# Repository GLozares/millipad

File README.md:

# MilliPad

## A First Step into the World of Keyboards
Hi there! If you're reading this, thank you for stopping by. This is a repository detailing my first foray into custom mechanical keyboards. I decided to make a custom mechanical keypad to use for myself as my favorite keyboard layout, the 65%, does not have F1 through F12. However, in some circumstances particularly when I am coding, I would like to have those function keys. Thus, instead of buying a numpad off the shelf, I thought it was a great opportunity to make my own.

Prior to this project, I took on a group project in my Computer Engineering senior design class that involves creating our own full sized custom mechanical keyboard. I took some initiative and began to learn PCB design myself as to be a bigger asset to my group down the line.

## Credits
Apart from the dependant repositories already linked in my project, I would like to thank ai03 for their beginner's tutorial on keyboard PCB design. Their guide can be found at https://wiki.ai03.com/books/pcb-design.

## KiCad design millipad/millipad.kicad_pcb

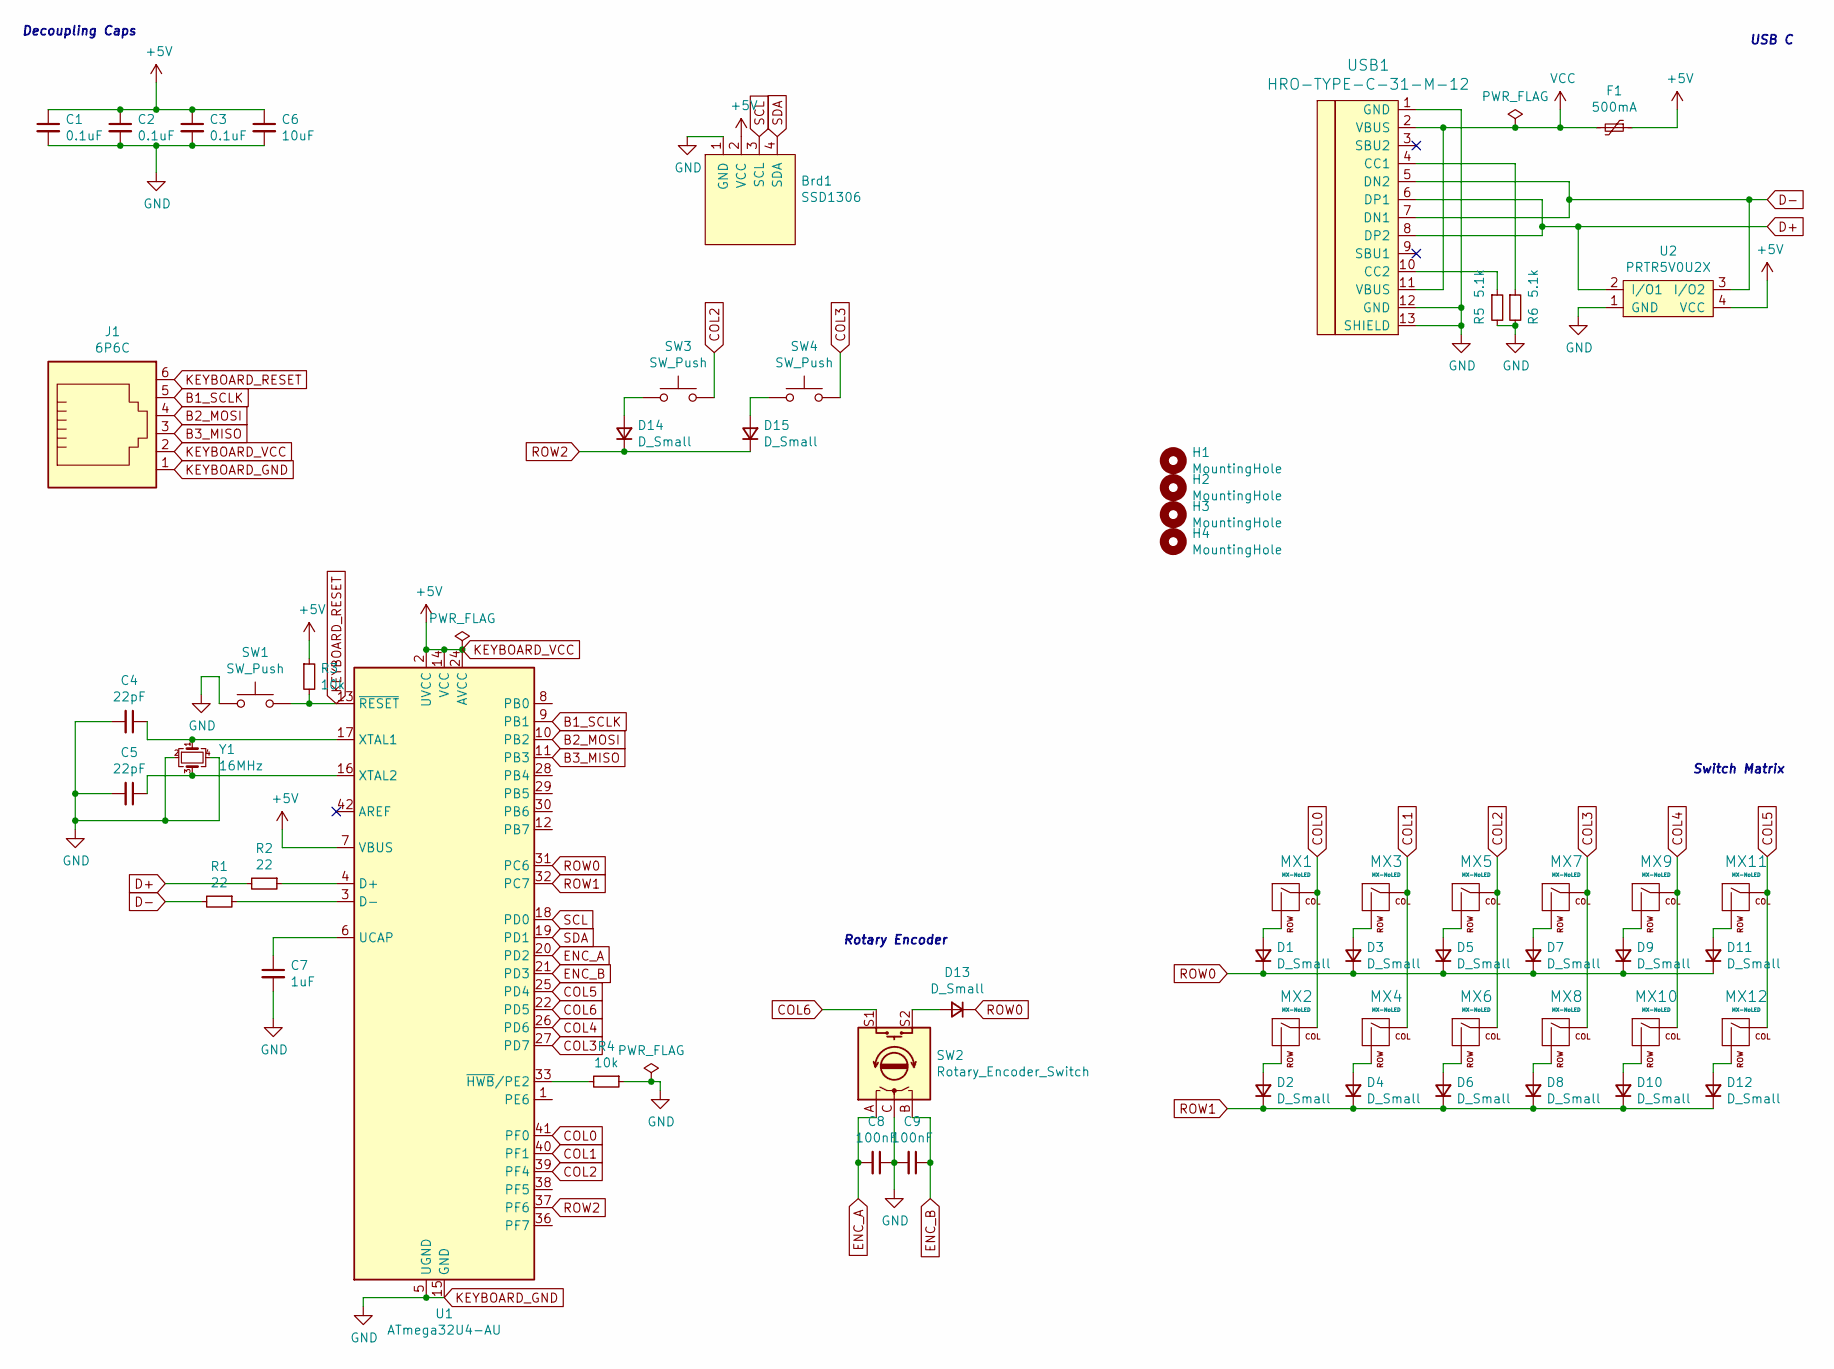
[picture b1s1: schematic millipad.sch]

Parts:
Brd1: SSD1306; 128x64OLED
C1, C2, C3: 0.1uF; C_0805_2012Metric
C4, C5: 22pF; C_0805_2012Metric
C6: 10uF; C_0805_2012Metric
C7: 1uF; C_0805_2012Metric
C8, C9: 100nF; C_0805_2012Metric
D1, D2, D3, D4, D5, D6, D7, D8, D9, D10, D11, D12, D13, D14, D15: D_Small; D_SOD-123
F1: 500mA; Fuse_1206_3216Metric
H1, H2, H3, H4: MountingHole; MountingHole_2.7mm_M2.5
J1: 6P6C; PinSocket_2x03_P1.00mm_Vertical_SMD
MX1, MX2, MX3, MX4, MX5, MX6, MX7, MX8, MX9, MX10, MX11, MX12: MX-NoLED; MXOnly-1U-Hotswap
R1, R2: 22; R_0805_2012Metric
R3, R4: 10k; R_0805_2012Metric
R5, R6: 5.1k; R_0805_2012Metric
SW1, SW3, SW4: SW_Push; SKQG-1155865
SW2: Rotary_Encoder_Switch; RotaryEncoder_Alps_EC11E-Switch_Vertical_H20mm
U1: ATmega32U4-AU; TQFP-44_10x10mm_P0.8mm
U2: PRTR5V0U2X
USB1: HRO-TYPE-C-31-M-12; HRO-TYPE-C-31-M-12-HandSoldering
Y1: 16MHz; Crystal_SMD_3225-4Pin_3.2x2.5mm

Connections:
B1_SCLK: J1.5, U1.9 (PB1)
B2_MOSI: J1.4, U1.10 (PB2)
B3_MISO: J1.3, U1.11 (PB3)
COL0: MX1.1 (COL), MX2.1 (COL), U1.41 (PF0)
COL1: MX3.1 (COL), MX4.1 (COL), U1.40 (PF1)
COL2: MX5.1 (COL), MX6.1 (COL), SW3.2, U1.39 (PF4)
COL3: MX7.1 (COL), MX8.1 (COL), SW4.2, U1.27 (PD7)
COL4: MX9.1 (COL), MX10.1 (COL), U1.26 (PD6)
COL5: MX11.1 (COL), MX12.1 (COL), U1.25 (PD4)
COL6: SW2.S1, U1.22 (PD5)
D+: R2.2, U2.2 (I/O1), USB1.6 (DP1), USB1.8 (DP2)
D-: R1.2, U2.3 (I/O2), USB1.5 (DN2), USB1.7 (DN1)
ENC_A: C8.2, SW2.A, U1.20 (PD2)
ENC_B: C9.1, SW2.B, U1.21 (PD3)
KEYBOARD_GND: Brd1.1 (GND), C1.2, C2.2, C3.2, C4.2, C5.2, C6.2, C7.2, C8.1, C9.2, J1.1, R4.1, R5.2, R6.2, SW1.1, SW2.C, U1.5 (UGND), U1.15 (GND), U1.23 (GND), U1.35 (GND), U1.43 (GND), U2.1 (GND), USB1.1 (GND), USB1.12 (GND), USB1.13 (SHIELD), Y1.2, Y1.4
KEYBOARD_RESET: J1.6, R3.2, SW1.2, U1.13 (~RESET)
KEYBOARD_VCC: Brd1.2 (VCC), C1.1, C2.1, C3.1, C6.1, F1.1, J1.2, R3.1, U1.2 (UVCC), U1.7 (VBUS), U1.14 (VCC), U1.24 (AVCC), U1.34 (VCC), U1.44 (AVCC), U2.4 (VCC)
unnamed: C4.1, U1.17 (XTAL1), Y1.1
unnamed: C5.1, U1.16 (XTAL2), Y1.3
unnamed: C7.1, U1.6 (UCAP)
unnamed: D1.2 (A), MX1.2 (ROW)
unnamed: D2.2 (A), MX2.2 (ROW)
unnamed: D3.2 (A), MX3.2 (ROW)
unnamed: D4.2 (A), MX4.2 (ROW)
unnamed: D5.2 (A), MX5.2 (ROW)
unnamed: D6.2 (A), MX6.2 (ROW)
unnamed: D7.2 (A), MX7.2 (ROW)
unnamed: D8.2 (A), MX8.2 (ROW)
unnamed: D9.2 (A), MX9.2 (ROW)
unnamed: D10.2 (A), MX10.2 (ROW)
unnamed: D11.2 (A), MX11.2 (ROW)
unnamed: D12.2 (A), MX12.2 (ROW)
unnamed: D13.2 (A), SW2.S2
unnamed: D14.2 (A), SW3.1
unnamed: D15.2 (A), SW4.1
unnamed: R1.1, U1.3 (D-)
unnamed: R2.1, U1.4 (D+)
unnamed: R4.2, U1.33 (~HWB~/PE2)
unnamed: R5.1, USB1.10 (CC2)
unnamed: R6.1, USB1.4 (CC1)
ROW0: D1.1 (K), D3.1 (K), D5.1 (K), D7.1 (K), D9.1 (K), D11.1 (K), D13.1 (K), U1.31 (PC6)
ROW1: D2.1 (K), D4.1 (K), D6.1 (K), D8.1 (K), D10.1 (K), D12.1 (K), U1.32 (PC7)
ROW2: D14.1 (K), D15.1 (K), U1.37 (PF6)
SCL: Brd1.3 (SCL), U1.18 (PD0)
SDA: Brd1.4 (SDA), U1.19 (PD1)
VCC: F1.2, USB1.2 (VBUS), USB1.11 (VBUS)

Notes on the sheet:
Decoupling Caps
USB C
Switch Matrix
Rotary Encoder

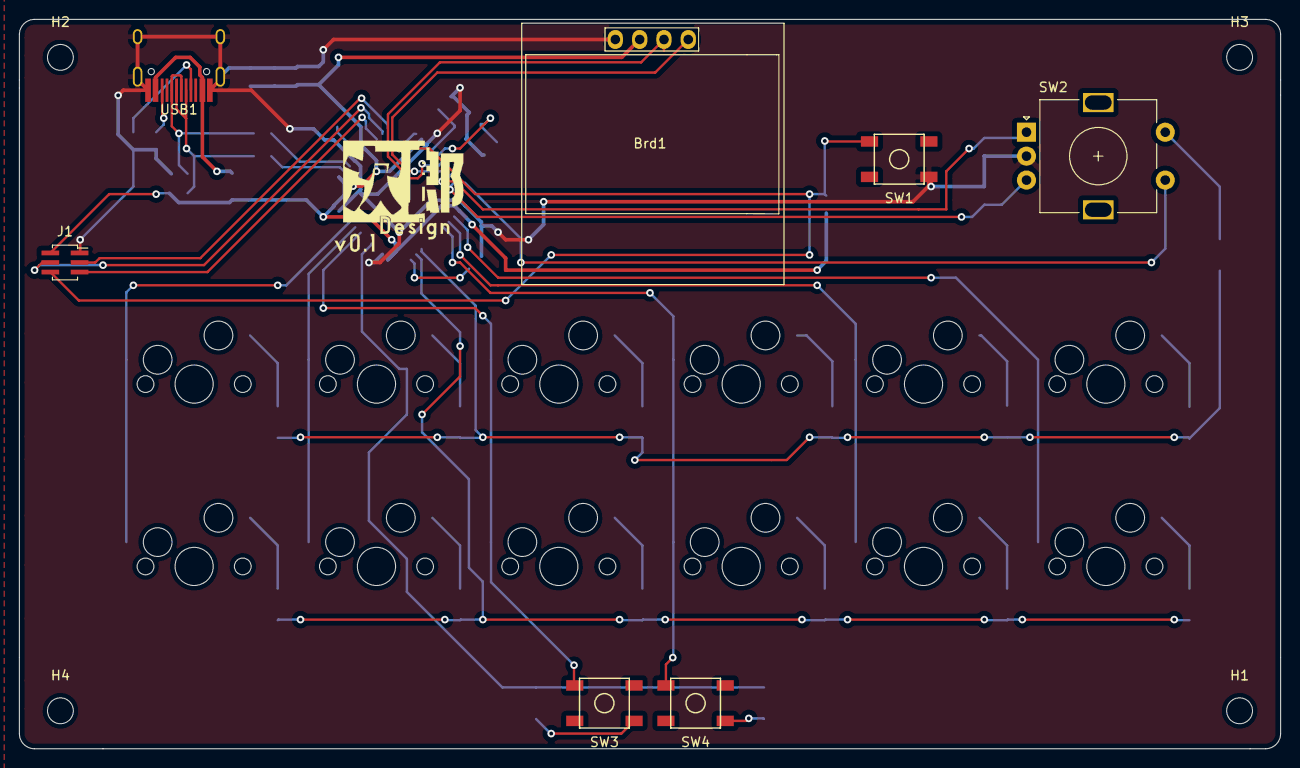
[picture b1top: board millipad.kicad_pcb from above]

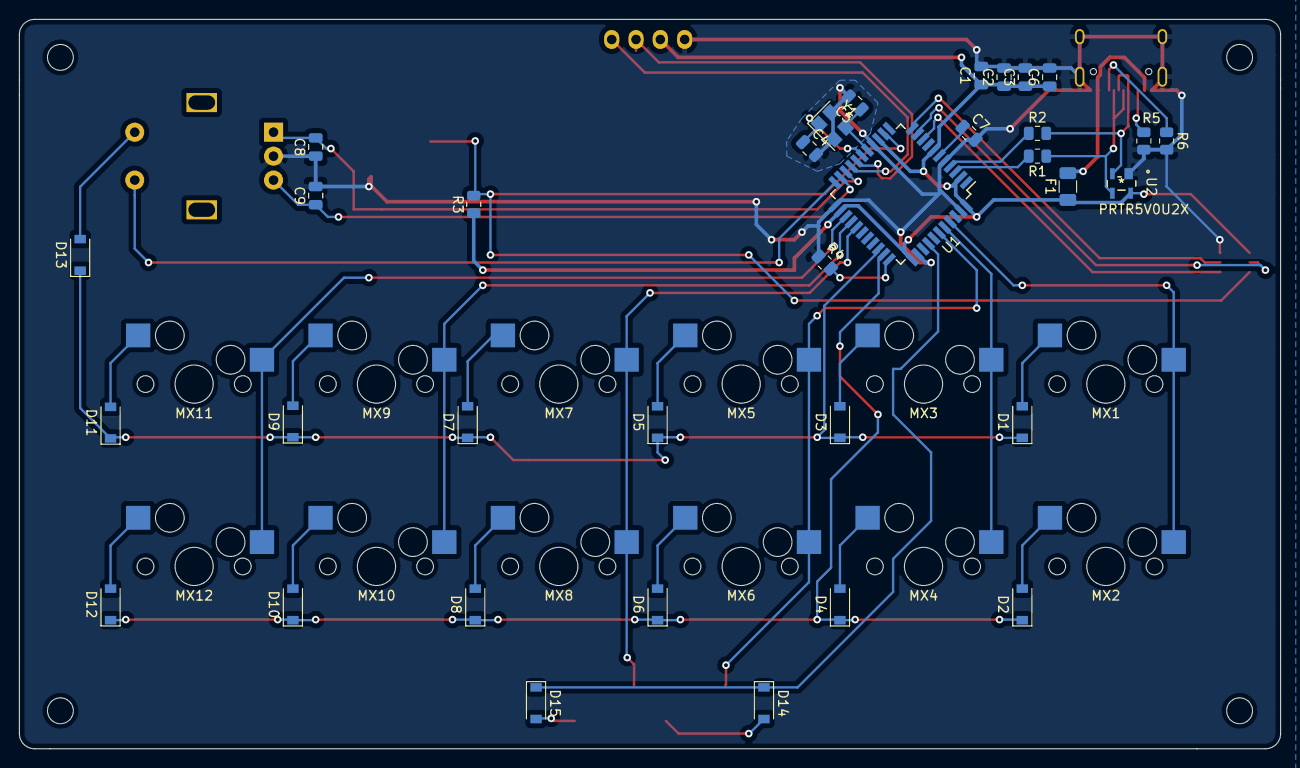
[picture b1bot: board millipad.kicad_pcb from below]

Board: 2 copper layers, 131.8 x 76.2 mm, 57 parts (34 on the bottom side), 46 nets.

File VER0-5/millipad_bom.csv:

Reference, Quantity, Value, Footprint, Datasheet
Brd1 ,1,"SSD1306","SSD1306:128x64OLED",""
C1 C2 C3 ,3,"0.1uF","Capacitor_SMD:C_0805_2012Metric","~"
C4 C5 ,2,"22pF","Capacitor_SMD:C_0805_2012Metric","~"
C6 ,1,"10uF","Capacitor_SMD:C_0805_2012Metric","~"
C7 ,1,"C_Small","Capacitor_SMD:C_0805_2012Metric","~"
C8 C9 ,2,"100nF","Capacitor_SMD:C_0805_2012Metric","~"
D1 D2 D3 D4 D5 D6 D7 D8 D9 D10 D11 D12 D13 D14 D15 ,15,"D_Small","Diode_SMD:D_SOD-123","~"
F1 ,1,"500mA","Fuse:Fuse_1206_3216Metric","~"
H1 H2 H3 H4 ,4,"MountingHole","MountingHole:MountingHole_2.7mm_M2.5","~"
J1 ,1,"6P6C","Connector_PinSocket_1.00mm:PinSocket_2x03_P1.00mm_Vertical_SMD","~"
MX1 MX2 MX3 MX4 MX5 MX6 MX7 MX8 MX9 MX10 MX11 MX12 ,12,"MX-NoLED","MX_Only:MXOnly-1U-Hotswap",""
R1 R2 ,2,"22","Resistor_SMD:R_0805_2012Metric","~"
R3 R4 ,2,"10k","Resistor_SMD:R_0805_2012Metric","~"
R5 R6 ,2,"5.1k","Resistor_SMD:R_0805_2012Metric","~"
SW1 SW3 SW4 ,3,"SW_Push","random-keyboard-parts:SKQG-1155865","~"
SW2 ,1,"Rotary_Encoder_Switch","Keebio-Parts:RotaryEncoder_Alps_EC11E-Switch_Vertical_H20mm","~"
U1 ,1,"ATmega32U4-AU","Package_QFP:TQFP-44_10x10mm_P0.8mm","http://ww1.microchip.com/downloads/en/DeviceDoc/Atmel-7766-8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"
U2 ,1,"PRTR5V0U2X","prtr5v:PRTR5V0U2X",""
USB1 ,1,"HRO-TYPE-C-31-M-12","Type-C:HRO-TYPE-C-31-M-12-HandSoldering",""
Y1 ,1,"16MHz","Crystal:Crystal_SMD_3225-4Pin_3.2x2.5mm","~"

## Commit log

2021-03-22 Added dependencies
2021-03-22 MCU Schematic
2021-03-22 PCB Layout
2021-03-23 3d work
2021-03-23 OLED Implementation WIP
2021-03-28 Rewired CPU to fit OLED
2021-03-28 Added SSD1306 128x64 OLED Breakout Board
2021-03-28 Added pushbutton and isp flash headers
2021-03-29 Generated BOM, POS, STEP for Plate Assembly
2021-04-05 Created manufacturing files for production and uploaded renders
2021-04-05 Made the readme something presentable
2021-04-08 firmware published
2021-04-08 Updated firmware files
2021-04-09 ground planes

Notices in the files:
parts and their libraries:
Copyright 2016 Accelerated Designs. All rights reserved.
